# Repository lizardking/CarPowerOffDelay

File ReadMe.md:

Car Turn Off Delay Relay Board
==============================

IDK how many times chargers for mobiles and other devices that were connected to out classic cars lighter plugs have drained 
the cars batteries to a point where is was impossible to start the car again (usualy after the car had not been used for a few weeks).

This board overcomes this problem by disconnecting the power supply to the lighter plug (or anything else) after a defineable period 
(up to approx. 135minutes) after the cars iginition has been turned off. Like this it is still possible to charges mobiles and the like
for a while after the car had been stopped, but not to a point where the cars battery is drained to much.

Once the board turns off the power on its output it also disconnects itself completely from the power supply and wont consume even the 
slightest bit off power in this state.

Design
------

The board was designed with the Eagle PCB editor. So if you want to make changes you'll need this software.

The boart uses a ATTiny microcontroller as its brain. This allows for easy modification of the boards behaviour. The firmware for the 
microcontroller has been written very quick and dirty with Bascom. Bascom might not be a nice solution, but for simple stuff like this
it is good enough. The hex and bin files for upload to the microcontroller are contained in the firmware folder, so you will not need 
Bascom and you can just use whatever tool you prefer to upload the firmware.

The parts on the board are all simple, stanard components which should be readily available at almost every electronic parts store.
The connectores are FASTON Automotive Connectors.

Installing the board
--------------------

* Connect the GND and 12V connectors to the battery of your car. They must have a uninterupted line to the battery, so no switch or the
  like on the way to the battery.
* Connect 12V Sense to the ignition switch of your car or any other line which will have 12V as long as the car is running and which will
  turn of when the engine is stopped.
* Connect 12V Out and GND Out to the lighter plug or any other appliance you want to turn off with a delay.

Configuring the time out/delay
------------------------------

To set the desired turn off delay,do the following:

* Turn the trimmer on the board to a value which is well above the desired target time. Max. time is when the timer is fully at the 5V end.
* Start the timer with a 12V pulse on the sense input and disconnect the sense input immediately.
* Let the time you want the timer to run elapse, e.g. use a time on your phone.
* Once the desired time has elapsed turn the trimer back towards the GND end till the timer stops/relay turns off.

Bingo! You have set the desired turn off delay time.

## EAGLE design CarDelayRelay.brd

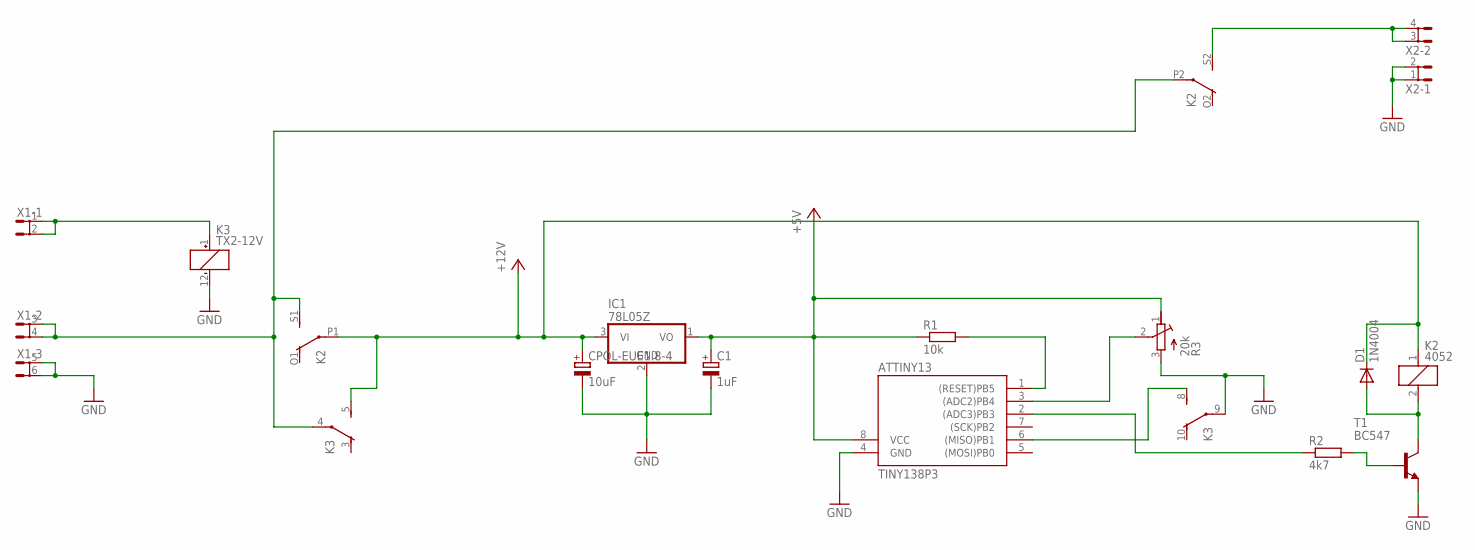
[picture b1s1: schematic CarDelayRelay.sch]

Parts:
ATTINY13: TINY138P3; DIL08
C1: 1uF; E1,8-4
CPOL-EUE1.8-4: 10uF; E1,8-4
D1: 1N4004; DO41-10
IC1: 78L05Z; TO92
K2: 4052; F4052
K3: TX2-12V; TX2
R1: 10k; 0204/7
R2: 4k7; 0207/2V
R3: 20k; RTRIM43P
T1: BC547; TO92
X1: SH5-3
X2: SH5-2

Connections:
+5V: ATTINY13.8 (VCC), C1.+, IC1.1 (VO), R1.1, R3.1 (A)
GND: ATTINY13.4 (GND), C1.-, CPOL-EUE1.8-4.-, IC1.2 (GND), K3.9, K3.12 (-), R3.3 (E), T1.1 (E), X1.5 (1), X1.6 (2), X2.1, X2.2
IC1: ATTINY13.6 ((MISO)PB1), K3.8 (S)
unnamed: K3.1 (+), X1.1, X1.2
unnamed: ATTINY13.1 ((RESET)PB5), R1.2
unnamed: ATTINY13.2 ((ADC3)PB3), R2.1
unnamed: R2.2, T1.2 (B)
unnamed: D1.A, K2.2, T1.3 (C)
unnamed: K2.P2, K2.S1 (S), K3.4, X1.3 (1), X1.4 (2)
unnamed: K2.S2 (S), X2.3 (1), X2.4 (2)
unnamed: ATTINY13.3 ((ADC2)PB4), R3.2 (S)
VCC: CPOL-EUE1.8-4.+, D1.C, IC1.3 (VI), K2.1, K2.P1, K3.5 (S)

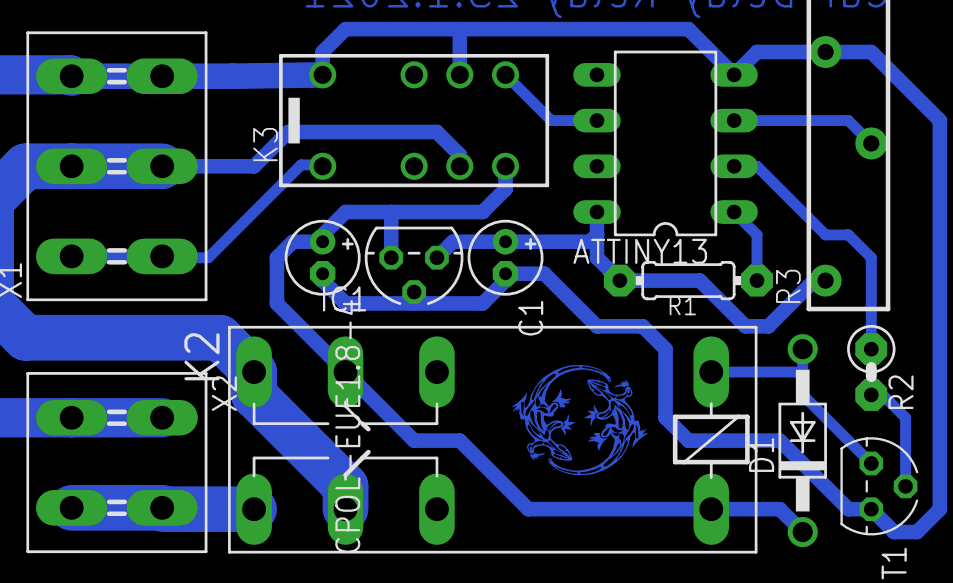
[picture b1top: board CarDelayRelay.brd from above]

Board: 2 copper layers, 14 parts (0 on the bottom side), 12 nets.

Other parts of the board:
CPOL-EUE1.8-1: BOTTOM_DOUBLE_LIZARD_300

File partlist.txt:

Partlist

Exported from CarDelayRelay.sch at 23.01.2021 15:21:43

EAGLE Version 6.4.0 Copyright (c) 1988-2013 CadSoft

Assembly variant: 

Part          Value          Device        Package  Library          Sheet

C1            1uF            CPOL-EUE1.8-4 E1,8-4   0_Standard-Parts 1
CPOL-EUE1.8-4 10uF           CPOL-EUE1.8-4 E1,8-4   0_Standard-Parts 1
D1            1N4004         1N4004        DO41-10  diode            1
IC1           78L05Z         78L05Z        TO92     linear           1
K2            4052           4052          F4052    Relay            1
K3            TX2-12V        TX2-12V       TX2      Relay            1
R1            10k            R-EU_0204/7   0204/7   0_Standard-Parts 1
R2            4k7            R-EU_0207/2V  0207/2V  0_Standard-Parts 1
R3            20k            R-TRIMM43P    RTRIM43P 0_Standard-Parts 1
T1            BC547          BC547         TO92     transistor       1
U$1           TINY138P3      TINY138P3     DIL08    0_avr            1
X1                           SH5-3         SH5-3    con-rib          1
X2                           SH5-2         SH5-2    con-rib          1

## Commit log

2021-01-24 readme update
2021-01-24 Create LICENSE
2021-01-24 Typo fixed
2021-01-24 Docu completed
